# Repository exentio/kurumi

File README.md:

# Kurumi

Addressable LED strip controller, based on the ESP32-C3 SuperMini.  
This is a shrinkage of a previous private project that was quite janky due to
my friend's needs.

**WARNING: the buck converter is currently not working properly.**

Designed to run at 5V or any voltage between 12V and 24V.  
In case of 5V strips, the buck converter part won't need to be populated;
instead, short jumper JP1's central pin to VCC.  
**DON'T DO THIS FOR ANY VOLTAGE OVER 5V OR YOU WILL FRY YOUR ESP32.**  

For strips running at 12V or more, short JP1 to INT (internal converter).  
**The buck converter is not designed for voltages over 24V.**  

The data pin is connected to GPIO5, at the moment no ESPhome or WLED
configuration has been made, you'll have to spin your own until I get the board
and test everything.  

The board also supports using relays or MOSFETs to cut power to the strip by
using the broken out pins J3. The EN pin is connected to GPIO4 and can be used
to control the switching device. Don't forget to short JP2 as needed, whether
you want to switch the power or not.  

It's recommended to add insulation over the jumpers and on unpopulated pads on
the bottom if the buck converter is not used (i.e. electrical or kapton tape).

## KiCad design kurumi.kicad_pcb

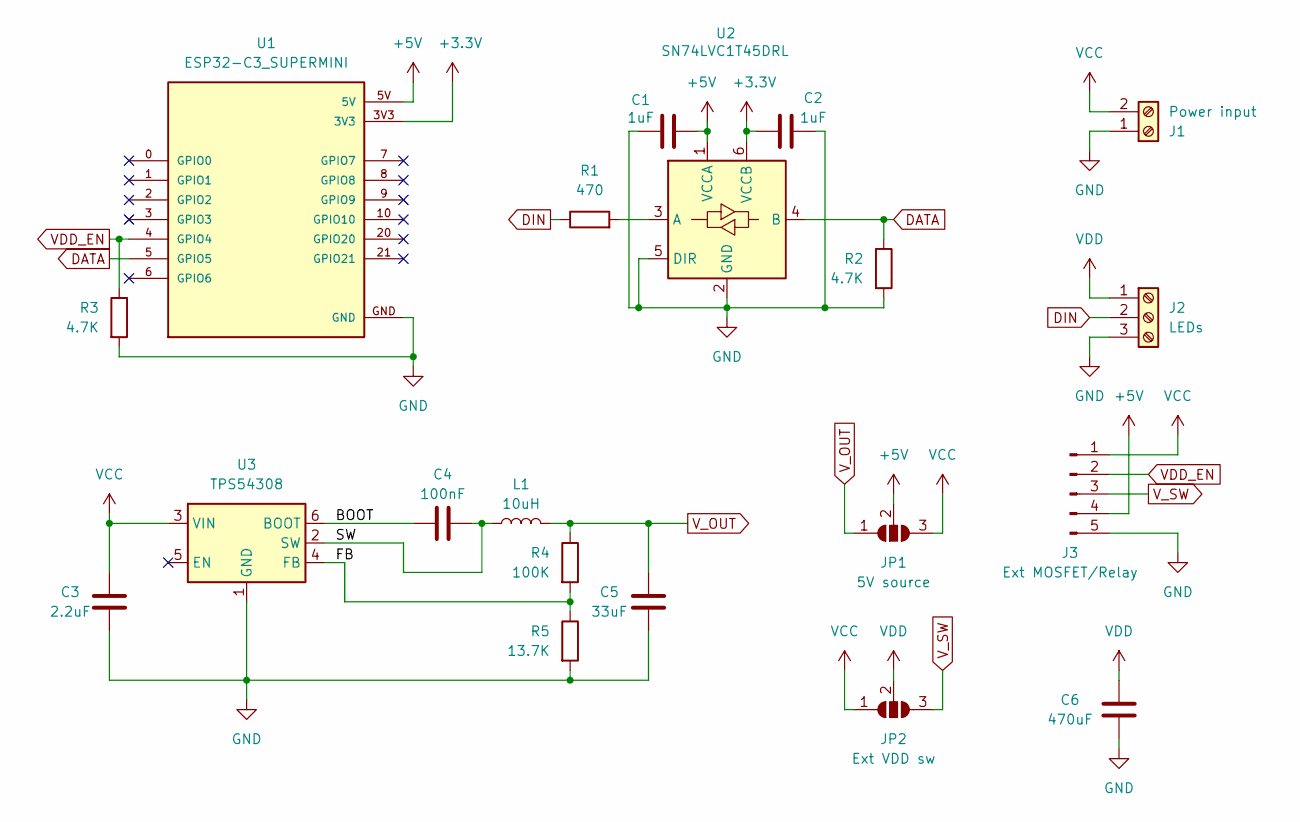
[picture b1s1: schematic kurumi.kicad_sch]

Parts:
C1, C2: 1uF; C_0603_1608Metric_Pad1.08x0.95mm_HandSolder
C3: 2.2uF; C_0603_1608Metric_Pad1.08x0.95mm_HandSolder
C4: 100nF; C_0603_1608Metric_Pad1.08x0.95mm_HandSolder
C5: 33uF; C_0805_2012Metric_Pad1.18x1.45mm_HandSolder
C6: 470uF; CP_Elec_8x10.5
J1: Power input; TerminalBlock_bornier-2_P5.08mm
J2: LEDs; TerminalBlock_bornier-3_P5.08mm
J3: Ext MOSFET/Relay; PinHeader_1x05_P2.54mm_Vertical
JP1: 5V source; SolderJumper-3_P1.3mm_Open_Pad1.0x1.5mm_NumberLabels
JP2: Ext VDD sw; SolderJumper-3_P1.3mm_Open_Pad1.0x1.5mm_NumberLabels
L1: 10uH; CYA0630
R1: 470; R_0603_1608Metric_Pad0.98x0.95mm_HandSolder
R2, R3: 4.7K; R_0603_1608Metric_Pad0.98x0.95mm_HandSolder
R4: 100K; R_0805_2012Metric_Pad1.20x1.40mm_HandSolder
R5: 13.7K; R_0805_2012Metric_Pad1.20x1.40mm_HandSolder
U1: ESP32-C3_SUPERMINI; MODULE_ESP32-C3_SUPERMINI_CASTELLATED
U2: SN74LVC1T45DRL; SOT-563
U3: TPS54308; SOT-23-6_Handsoldering

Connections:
+3.3V: C2.2, U1.3V3, U2.6 (VCCB)
+5V: C1.1, J3.4, JP1.2 (C), U1.5V, U2.1 (VCCA)
/BOOT: C4.2, U3.6 (BOOT)
/FB: R4.2, R5.1, U3.4 (FB)
/SW: C4.1, L1.1, U3.2 (SW)
DATA: R2.1, U1.5 (GPIO5), U2.4 (B)
DIN: J2.2, R1.1
GND: C1.2, C2.1, C3.2, C5.2, C6.2, J1.1, J2.3, J3.5, R2.2, R3.2, R5.2, U1.GND, U2.2 (GND), U2.5 (DIR), U3.1 (GND)
unnamed: R1.2, U2.3 (A)
VCC: C3.1, J1.2, J3.1, JP1.3 (B), JP2.1 (A), U3.3 (VIN)
VDD: C6.1, J2.1, JP2.2 (C)
VDD_EN: J3.2, R3.1, U1.4 (GPIO4)
V_OUT: C5.1, JP1.1 (A), L1.2, R4.1
V_SW: J3.3, JP2.3 (B)

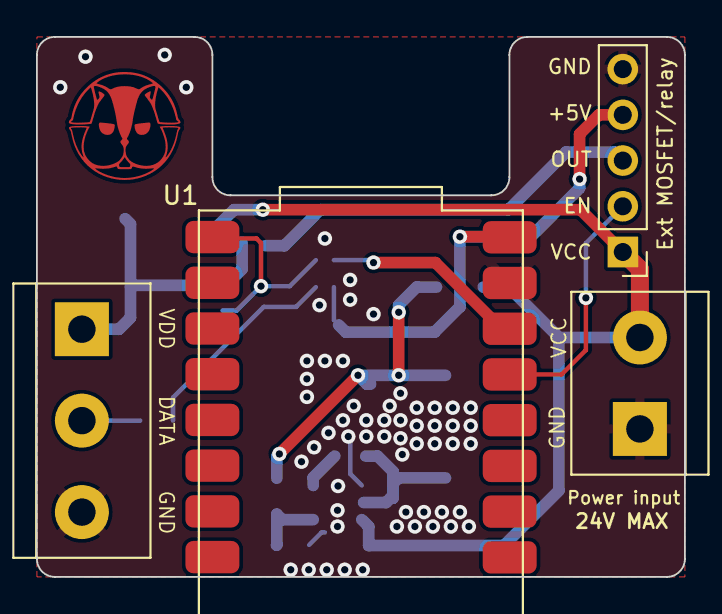
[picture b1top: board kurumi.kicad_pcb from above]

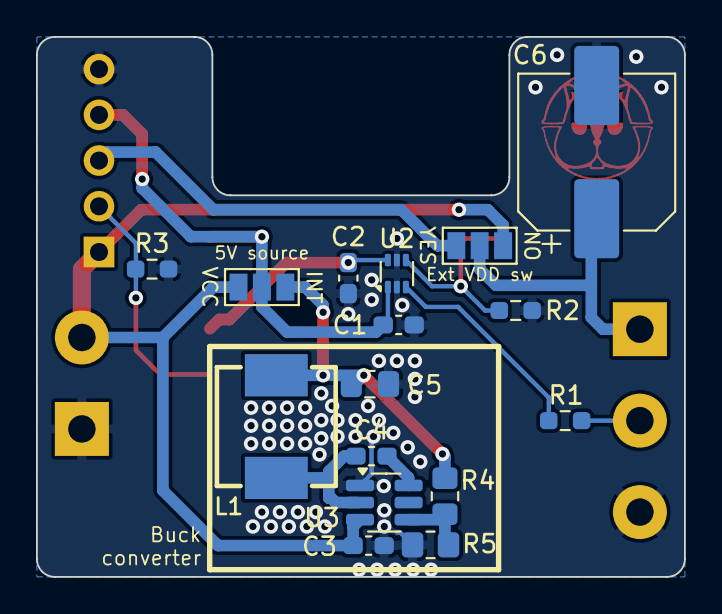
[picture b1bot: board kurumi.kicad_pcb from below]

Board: 2 copper layers, 36.0 x 30.0 mm, 20 parts (16 on the bottom side), 14 nets.

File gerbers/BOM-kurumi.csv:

Comment,Designator,Footprint,LCSC,Quantity
100nF,C4,C_0603_1608Metric_Pad1.08x0.95mm_HandSolder,C1591,1
1uF,"C1,C2",C_0603_1608Metric_Pad1.08x0.95mm_HandSolder,C1592,2
TPS54308,U3,SOT-23-6_Handsoldering,C168839,1
100K,R4,R_0805_2012Metric_Pad1.20x1.40mm_HandSolder,C1859593,1
2.2uF,C3,C_0603_1608Metric_Pad1.08x0.95mm_HandSolder,C307463,1
13.7K,R5,R_0805_2012Metric_Pad1.20x1.40mm_HandSolder,C317432,1
33uF,C5,C_0805_2012Metric_Pad1.18x1.45mm_HandSolder,C342635,1
SN74LVC1T45DRL,U2,SOT-563,C352970,1
470,R1,R_0603_1608Metric_Pad0.98x0.95mm_HandSolder,C491208,1
10uH,L1,CYA0630,C5189958,1
470uF,C6,CP_Elec_8x10.5,C7471889,1
4.7K,"R2,R3",R_0603_1608Metric_Pad0.98x0.95mm_HandSolder,C844791,2

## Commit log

2024-03-27 Cleanup
2024-03-27 Footprint and readme update
2024-03-27 Added libraries
2024-03-27 Readme update
2024-03-27 Gerbers update
2024-03-27 Parts updates, BOM and CPL
2024-03-28 Gitignore update
2024-05-15 Add license
2024-05-15 Minor changes
2024-05-15 Addes USB slot, fixed libraries
2024-05-15 Images update
2024-06-19 Buck converter fix by @CRImier
2024-07-21 Gerbers and JLCPCB files update
2024-07-22 BOM and CPL update
2024-12-28 Fix JLCPCB rotations
2025-01-10 Broken out 5V for relays and more
2025-01-10 Readme images update
